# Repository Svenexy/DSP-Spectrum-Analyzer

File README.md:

# DSP-Spectrum-Analyzer
DSP school project

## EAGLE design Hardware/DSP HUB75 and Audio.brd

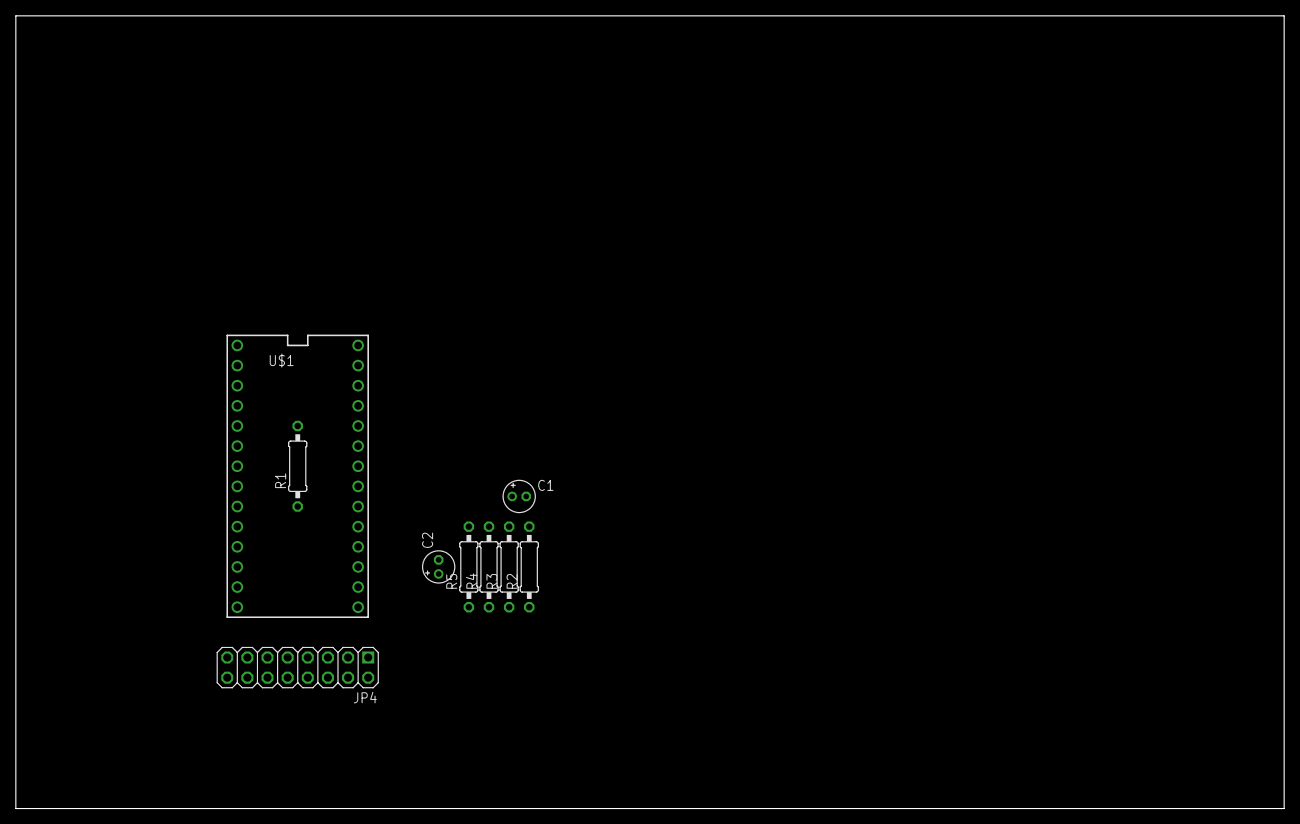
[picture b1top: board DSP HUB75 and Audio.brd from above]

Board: 2 copper layers, 160.0 x 100.0 mm, 9 parts (0 on the bottom side), 19 nets, no tracks yet.

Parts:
C1, C2: 10uF; E1,8-4
JP4: 2X08
R1: 1k; 0207/10
R2, R3: 47k; 0207/10
R4: 10k; 0207/10
R5: 2.2k; 0207/10
U$1: TEENSY_3.1-3.2_DIL; TEENSY_3.0-3.2&LC_DIL

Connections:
+3V3: R4.2, U$1.VIN
AUDIO_IN: C1.-, R2.2
FFT: C1.+, R3.2, U$1.16/A2
GND: C2.-, JP4.4, JP4.8, JP4.16, R2.1, R5.1, U$1.GND
unnamed: R1.2, U$1.3
unnamed: C2.+, R3.1, R4.1, R5.2
PANEL_ADX0: JP4.9, U$1.9
PANEL_ADX1: JP4.10, U$1.10
PANEL_ADX2: JP4.11, U$1.22/A8
PANEL_ADX3: JP4.12, U$1.23/A9
PANEL_B1: JP4.3, U$1.6
PANEL_B2: JP4.7, U$1.20/A6
PANEL_CLK: JP4.13, U$1.14/A0
PANEL_G1: JP4.2, U$1.5
PANEL_G2: JP4.6, U$1.7
PANEL_LATCH: JP4.14, R1.1, U$1.8
PANEL_OE: JP4.15, U$1.4
PANEL_R1: JP4.1, U$1.2
PANEL_R2: JP4.5, U$1.21/A7
